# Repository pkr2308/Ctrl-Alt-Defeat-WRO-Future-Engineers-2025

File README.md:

# This repository has been moved to [CmdOptDefeat/fe25](https://github.com/CmdOptDefeat/fe25)

<picture>
  <source media="(prefers-color-scheme: dark)" srcset="https://github.com/pkr2308/Ctrl-Alt-Defeat-WRO-Future-Engineers-2025/blob/main/repo-assets/logo/ctrlaltdefeat-no-glow-no-bg-4096.png">
  <source media="(prefers-color-scheme: light)" srcset="https://github.com/pkr2308/Ctrl-Alt-Defeat-WRO-Future-Engineers-2025/blob/main/repo-assets/logo/ctrlaltdefeat-no-glow-no-bg-dark-4096.png">
  
</picture>

<br><br>Welcome to the repository for our entry in the WRO Future Engineers 2025 competition!
We are a team of 2 aspiring engineers building an autonomous robotic car using Raspberry Pi 5 & RP2040, equipped with various sensors and custom designs.

# About the Team
Adbhut Patil: TODO: expand 10th standard, interested in electronics, programming, aviation

Pranav Kiran Rajarathna: Pranav is currently sudying in the 11th grade(PCMC combination) and has been interested in Robotics for several years . He has participated in WRO in other categories in the past years. He was also part of Coding club in his school and built a few robotics projects for school events. His other interests include maths, physics, numismatics and history.

| __Team Photo__ |
|:-----------:|
||
| __Picture: Pranav (Left) and Adbhut (Right)__ |

# Project Overview
This project is our official entry for the Future Engineers category at the World Robot Olympiad 2025. Our goal is to construct a self-driving vehicle capable of navigating the track in both the Open and Obstacle Rounds. The programs are written in C++ and Python in the VSCode IDE, with the PlatformIO extension. OpenCV is used with the Raspberry Pi for object detection and navigation. This repository contains the programs, hardware description, schematics and design files of our solution.

# Hardware Components
- __Compute:__ Raspberry Pi 5 (main computer), Raspberry Pi 2040 (Waveshare RP2040-Zero, real-time control)
- __Sensors:__ 1D and 2D LiDAR, IMU, rotary encoders, Picamera
- __Actuators:__ N20 geared DC motor with encoder, MG996R 180° servo
- __Chassis:__ Commercially available base with 3D-printable additions (3D-design files included)
- __Electronics:__ Custom peripherals interface PCB for reliable connections to sensors

Note: The whole readme file is massive.
See [this section](https://github.com/pkr2308/Ctrl-Alt-Defeat-WRO-Future-Engineers-2025?tab=readme-ov-file#peripherals-interface-board) for more details about sensors on the peripherals interface board, and <link> for details about the RPi 5 and its sensors.

# Repository Structure
- [design-files](https://github.com/pkr2308/Ctrl-Alt-Defeat-WRO-Future-Engineers-2025/tree/main/design-files) : Contains the Bill of Materials, 3D-printable design files and hardware. Pictures and description of the robot and components are included.
- [initial-tests](https://github.com/pkr2308/Ctrl-Alt-Defeat-WRO-Future-Engineers-2025/tree/main/initial-tests) : Intial tests on various sensors to ensure accurate data collection and basic object detection algorithm.
- [hw](https://github.com/pkr2308/Ctrl-Alt-Defeat-WRO-Future-Engineers-2025/tree/main/hw) : Contains schematic and PCB files for the peripherals interface board.
- [sw](https://github.com/pkr2308/Ctrl-Alt-Defeat-WRO-Future-Engineers-2025/tree/main/sw) : Contains PlatformIO project for the peripherals interface board.
- [open-round](https://github.com/pkr2308/Ctrl-Alt-Defeat-WRO-Future-Engineers-2025/tree/main/open-round) : It contains the program files for the open round over various iterations and hardware setups. The final open round program is found in `sw/peripherals-board/src/divers`
- [repo-assets]() :
- [obstacle-round](https://github.com/pkr2308/Ctrl-Alt-Defeat-WRO-Future-Engineers-2025/tree/main/obstacle-round) : 
- [test-data-recordings/open-round](https://github.com/pkr2308/Ctrl-Alt-Defeat-WRO-Future-Engineers-2025/tree/main/test-data-recordings/open-round) : It contains data logs from various open round tests

> [!NOTE]
> Random files called `.lgd-nfy0` may be seen sometimes in varioues places. These were probably created by a typo a long time ago, and despite repeated deletion, they keep spawning everywhere in the Pi's cone of the repo! Just ignore them, if they occur. 

# System Architecture 

-	Raspberry Pi 5: It uses ROS2 and handles more complex tasks like object and colour detection, route planning, and the 2D LiDAR
-	RP2040 (Pi Pico): Handles real-time tasks (motor PID, encoder feedback, servo control, IMU, 1D LiDAR)
-	LiDARs: Used for detecting turn direction, obstacles and in parking
-	IMU: Gives yaw (and other orientations) of the robot in [0,360)
-	Motor/Servos: PWM and PI controls respectively for movement using sensor data, coordinated by the RP2040

## Mobility

- A commercially available metal [chassis base](https://www.elecrow.com/4wd-smart-car-robot-chassis-for-arduino-servo-steering.html) has been used with custom designed and printed parts. This chassis was selected mainly for its good steering system, mobility and customisabilty (there are lots of through holes through the base-frame). While the steering was retained, the remaining parts were custom designed.
- A link based steering system is used in the robot with a link-rod between the front wheel joints and another between a wheel joint and the servo. This steering system has been taken from the chassis without much modification due to its precision. A MG996R 180° servo has been used for the steering due to its high torque and accuracy, which improve mobility. 
- A single axle rear drive train is used for driving is used. A 200RPM N20 motor is used due to its speed and decent torque. A 1:1 gear ratio is used with a pair of brass gears. Bearings are used on the rear axle for smooth movement. A custom [rear drive holder](https://github.com/pkr2308/Ctrl-Alt-Defeat-WRO-Future-Engineers-2025/blob/main/design-files/N20%20Motor%20Holder.stl) is used to house all these parts.
- Both the servo and N20 motors are connected to the peripherals board. The servo is controlled using the standard library, while PWM is used for speed control of the motor.
- Turning Radius: Optimized for narrow WRO track corners, and is 32-33 cm.
- Build Choice Reasoning: Offers realistic car-like dynamics, ideal for FE challenge simulation.
[Design files](https://github.com/pkr2308/Ctrl-Alt-Defeat-WRO-Future-Engineers-2025/tree/main/design-files) contains all the other custom 3D-Design files (created on [TinkerCAD](https://www.tinkercad.com)) for mounting various compnents and systems onto the base chassis and one another.
[Robot assembly](https://github.com/pkr2308/Ctrl-Alt-Defeat-WRO-Future-Engineers-2025?tab=readme-ov-file#robot-assembly) instructions are below.
- Improvements: 
1. A uniform steering system. In the current model, the servo has to turn a greater angle left than right for the same angles of the wheels in each direction. This complicates driving algorithms to some extent. A better, but equally smooth steering system, maybe a rack-and-pinion, will solve these issues.
2. Better gear train. The current gears, though made of brass wear down quite easily for some unidentified reason. This causes slipping if there is more wear.
3. Reducing the turning radius. The current bot, while quite manoeuvrable has a large turn radius (almost 33-34cm). Reducing this would make taking tighter turns possible, improving error margins in the obstacle round. This can be done by bringing the drive train forward.

## Power

- A [Waveshare UPS Hat E](https://www.waveshare.com/wiki/UPS_HAT_(E)) is used for powering the robot. It uses 4 4000mAH 3.6V 21700 Li-ion batteries. (Different battery capacities may be used). All outputs are at 5V.
- The Pi is powered at a stable 5V via the POGO pins on the UPS Hat. The PiCamera and RPLidar are power from the Pi.
- The RP2040 and all connected sensors are powered through a USB A-C cable from the Pi to it.
- The total current draw for the obstacle round is around 600-630mA, and around 250-300mA for idle with the Pi.
- The peripherals board gets power directly from the UPS Hat through a USB-A cable that has been cut to get the power wires. This powers only the rear motor and steering servo.
- Improvements:
1. The UPS Hat that we are using has a weird anomaly. Although the batteries will have good voltage output and detected capacity, it will show the net remaining capacity to be very low. We have edited the code of the UPS library to not allow it run `sudo poweroff` when it misdetects such a situation.
2. Maybe not have the small switch on the board; closing it will cause these 2 systems to be connected, which could lead to some bad outcomes!

## Sensors

- __TFLuna LiDAR:__ These are 1D-LiDARs that are used to measure distances to the front, left, right (for driving) and back(parking) of the robot. They are connected to the RP2040. A separate section has been designed at the front of the robot to house all four LiDARs. Each LiDAR has 5 wires, grouped into 4+1 (I2C + GND) going into the peripherals board. These LiDARs were selected for their accuracy, small size and ease of use.
- __BNO055:__ This is the IMU we are using for orientation due to its reliability, accuracy and simplicity of use. It is connected to the RP2040, and is directly slotted into the peripherals board.
- __nRF24L01:__ This is the wireless module used for wireless communication during testing and debugging with the RP2040. Another custom module (telemetry board) is made for receiving the data. (Note : This is not plugged in for actual rounds). It is directly slotted into the peripherals board.
- __Motor encoders:__ The encoders give ticks each time they are trigerred by rotation of the motor shaft. Data from it is used for distance calculations. In our case, about 43 ticks corresponds to 1cm. The 4 encoder wires are grouped together and connected to the peripherals board.
- __Raspberry Pi Camera Module 3 Wide:__ It is used with the Pi for detecting the an obstacles. The camera is secured at four points for greater stability. With only two connection points, the camera could be easily turned due to the material properties of the Camera to Pi 5 connection wire. The higher mounting location allows it to detect obstacles from a large distance (almost 2m!) and plan accordingly. The Wide lens allows for a greater field of view. The NoIR version used to give odd red patches due to the lack of the IR filter in some test cases.
- __RPLidar A1:__ It is a 2D-LiDAR. It was supposed to be connected to the Pi and give distance all around the robot. However, we could not get it work Raspbian or any other OS. (It worked well with ROS though!) So, it is basically dead weight!
- Improvements: 
1. The RPLidar doesn't work well with the standard Raspbian OS on the Pi or with a computer, with values for many angles returned zero or being frozen. It seems to work fine on ROS though. Not sure what the issue is, but resoving this can improve ease of programming.
2. The 1D LiDARs are quite expensive. Ultrasonic sensors would have done for the sides.
3. The BNO055 does clock stretching, which causes issues on the I2C buses of most microcontrollers (thankfully not the RP2040). It also has a slight drifting tendency of a few degrees after a round. A IMU that does not have these issues and is easy to use will be more accurate and more flexible in use.

The [Bill of Materials](https://github.com/pkr2308/Ctrl-Alt-Defeat-WRO-Future-Engineers-2025/blob/main/design-files/Bill%20of%20Materials.md) contains all necessary parts/components and their sources.

## Obstacle Management

- This is done mainly using the camera feed from the PiCamera 3 Wide. The NoIR version tends to give red spot in places with lots of light due to lack of IR filter, which made it incompatible for this case.
- The OpenCV library (in Python3) is used for all the image manipulation and data extrapolation. HSV mode has been used for all the detecting, while images arer displayed in RGB. Sometimes, red may appear as blue due to use of BGR format used by camera to rercord. This is of no consequence, since it does not affect detection itself.
- Initially, the colour ranges for the obstacles, parking walls and side walls are identified. Interestingly, in our case, the 'magenta' parking walls show up as pure red.
- First, the region of interest (ROI) is taken as the bottom half of the feed (this is for our camera placement. May vary for other setups).
- Then, coloured masks (one each for red and green) are applied, followed by OpenCV's controur detection to detect surfaces. Data like position, height and width of the contours may be obtained from the other OpenCV methods.
- If the contours detected meet the required criteria (like size, height-width ratio), they are classified as obstacles. For our benefit, rectangles are drawn around the obstacles.
- Using the data available, including obstacle position, yaw and distance travelled, the required steering is calculated to pass the obstacle on the correct side, when not at a turn (Red - right, green - left)
- When the side chosen is preceded by a turn, the turn is initiated at a predefined distance from the wall ahead. (Ex: Clockwise round, green -> turn early)

Improvements:
1. The RPLidar might have been used effectively with better drivers with the standard Raspbian OS.
2. A more accurate formula to convert y-coordinate of obstacle obtained by the camera into actual distance

# Robot Assembly

It will be helpful to refer to the pictures of the completed model for the following steps. Most screws used are of 3M type (3mm dia.). At some places in our robot, internal hex screws are used in places where plus(+) screws of the right length were not available.
1. Add the front wheels and steering link to the robot
2. Attach the servo motor and connect it to the steering link
3. Print all design files
4. Attach the N20 motor onto the rear drive with brackets. Fit a gear onto the motor.
5. Cut the rear axle to the appropriate length (around 96mm) and attach the rear axle with wheels and gear onto the rear drive.
6. Mount the rear drive onto the chassis.
7. Attach 6 pillar screws of length 26mm in the back and 2 of length 22mm in the front (adjacent to the servo)
8. Attach the middle plate at the 6 rear points, but not at the front. The peripherals board may be screwed on using 4 pillar screws.
9. Attach the TFLuna LiDARs to the front LiDAR holder section, followed by the RPLiDAR (remember to connect the USB adapter) with 22/24 mm screw pillars. Screw in the front points.
10. Attach the LiDAR holder section to the front of the chassis.
11. Attach the additional support section for the LiDAR holder to the 2 front middle plate points and 2 rear RPLidar points.
12. Screw in the RPLidar's extra micro-USB pin extender to the support section
13. Attach the two PiCamera holder parts to the rear of the Lidar support section, and screw in the camera (2M screws and nuts are needed)
12. Attach the top-most Raspberry Pi and UPS platform to the rear with screw pillars.
13. Attach the rear lidar holder with the rear lidar attached to it
14. Attach the Raspberry Pi with the UPS Hat to the top.
15. Make all wired connections by referring to schematic files.

# Peripherals Interface Board

The peripherals interface board goes between the Raspberry Pi and vehicle hardware. The board talks to three 1d TFLuna LiDARs, a 9-axis BNO055 IMU, the motor encoder, the drive motor, and the steering servo. It talks to the Pi over USB.

## Hardware
The board is a two-layer, 1.6 mm thick PCB designed in [KiCad](https://kicad.org) and manufactured by [Robu](https://robu.in).
TODO: Expand

## Software
The interface board was programmed in C++, with the C++ SDK from Raspberry Pi for the RP2040 chip. Code was flashed using the PlatformIO extension for the VSCode editor.

The codebase is designed to be modular, with easily swappable drivers for hardware abstraction. Algorithms do not need to know about specific hardware protocols or constraints

`main.cpp` loads in drivers, which implement virtual interface classes. `main.cpp` then initialises everything, and in a loop, gets data from the `SensoorManager`, passes that data to our drive algorithm, and outputs it to the `TargetController`, which commands the motor and steering servo.
Drivers are in `/src/drivers`, Interfaces are in `/src/interfaces/`, and utilities are in `/src/utils/`.

### Code Development Standards
To ensure easily testable, upgradeable, and clean code, a few standards were adhered to when writing code for the interface board.

- `main.cpp` must be as clean as possible.
  - Logic and code flow must be easy to understand.
- All hardware-specific things should be done inside a driver.
- Drivers must take in a standard unit as their input.
  - Drivers must not take in [magic numbers](https://en.wikipedia.org/wiki/Magic_number_(programming)).

TODO: Finish writing this

### Drivers
> [!NOTE]
> Hardware revision 1 drivers are incomplete, as the peripherals baord codebase was partly written when the switch from the prototype interface and the PCB occured, and drivers from that point on were only for the PCB (hardware revision 2).
A list of implemented drivers:
- `hwrev2_imu` : Implements `ISensor`. Driver for the BNO055. Gets orientation data processed by the BNO055's internal microcontroller.
- `hwrev2_lidar` : Implements `ISensor`. Driver for the TFLuna LiDARs. Returns a [0, 259] of distance data. The three LiDARs are mapped to `0`, `90`, and `270`. (This is a remnant of the original plan of connecting the RPLidar to the peripherals board, instead of to the Pi.)
- `hwrev2_motor_driver` : Implements `IMotorDriver`. Driver for the TB6612FNG dual-channel H-bridge motor driver. The driver only supports driving a single channel on the T66612FNG.
- `hwrev2_rf24_communication` :  Implements `ICommunication`. Driver for the nRF24L01+ radio used during development. Transmits vehicle data and gets commands from another nRF24L01+, connected to a computer.
- `hwrev2_single_lidar_open_round` : Implements `IDriveAlgorithm`. A port of our open round test algorithm. The name is misleading, the algorithm uses all three TFLunas.
- `hwrev2_steering_driver` : Implements `ISteeringDriver`. Driver for the MG996 steering servo. Takes in a degree input and coverts it to a 0-180 command with a conversion constant.
- `hwrev2_target_control` : Implements `ITargetControl`. Takes in a `VehicleCommand`, and either passes it directly through to the `ISteeringDriver` and `IMotorDriver`, or passes the command through a PID controller first.
- `hwrev2_uart_logger` :  Implements `ILogger`, Takes in a sender, message type, and a message string
- `hwrev2_vehicle_speed` : Implements `ISensor`. Gets vehicle distance from the motor encoder. Calculates speed using time between pulses.

### Interfaces

Interfaces are virtual classes which define certain functions. Drivers implement these classes. Code calls functions defined in the interface virtual class.

- `IDriveAlgorithm` : Takes in a `VehicleData` object, and returns a `VehicleCommand` object.
- `ILogger` : Constructs a message and prints it out on a UART bus. Takes in a sender string, a log type (information, warning, error) and the message.
- `IMotorDriver` : Takes in a speed value and outputs to a motor driver.
- `ISensor` :  A generic sensor object. Returns a vector of `SensorData` objects.
- `ISteeringDriver` :  Takes in a wheel steering angle, outputs to a steering mechanism.
- `ITargetControl`: Takes in a `VehicleCommand`, outputs to a motor and steering driver.

### Managers

Managers are classes that handle certain aspects of the vehicle. Certain structs have their header files in the `/src/managers` folder, even though they are not classes.

- `VehicleConfig` :  A struct containing information about the vehicle. A `VehicleConfig` struct is passed to all drivers asnd managers.
- `SensorData` :  A struct containing fields for all data that can be collected by the vehicle, and an enum which tells the caller what fields are being used.
- `SensorManager` :  A class which takes in an arbitrary number of sensors, collects data from them, and processes them into a `VehicleData` struct.
- `SensorStatus` :  A (currently unused) enumeration which defines keys for states a sensor can be in. 
- `Vec3f` :  A struct of three double-precisionn floating point numbers, used to represent three-axis values.
- `VehicleCommand` :  A struct defining a target speed and yaw value for the vehicle. Returned by a drive algorithm, passed to a `ITargetController`.
- `VehicleData` :  A struct containing processed vehicle data. Returned by a `SensorManager`.

## Utilities

- `SchedulerTask` : A class which calls a function periodically.
- `Schedular` : A class which takes in an arbitrary number of `SchedulerTask`s, and updates them.

# Raspberry Pi System

The Raspberry Pi system handles most tasks for the obstacle round, including unparking, obstacle detection and navigation.

## Raspbian Setup

We are using Raspbian Bookworm.
Run the following commands in the terminal
- $`sudo chmod 0700 /run/user/1000`
- $`sudo apt install software-properties-common`
- $`sudo apt install python3-launchpadlib`
- $`sudo apt install code`
- $`sudo apt upgrade code`
- $`sudo apt install idle3`
- $`sudo apt install python3-opencv`
- $`sudo apt install -y python3-libcamera python3-pyqt5 python3-picamera2`
- Refer [here](https://www.waveshare.com/wiki/UPS_HAT_(E)) to install UPS library to show details about the batteries.
- If the Pi is accidentally shut down, and git is not working, run the following: 
1. $`find .git/objects/ -type f -empty | xargs rm` - Cleaning
2. $`git fetch -p` - Restore missing objects
3. $`git fsck --full` - Verify
- It is advised to have RPiConnect for easy connection to the Pi.
- This reposittory is cloned on the Pi and the obstacle round program is added to the startup sequence.

## Adding Programs to Startup

The method used here involves running executables on startup. Refer [`initial-tests/startup-test/`](https://github.com/pkr2308/Ctrl-Alt-Defeat-WRO-Future-Engineers-2025/tree/main/initial-tests/startup-test) for the code.
1. Create the python file
2. Create a launcher script, like the one in the initial test file, that ends in `.sh`. Ensure the launcher is working with `./(launcher-name).sh` in its directory.
3. In the launcher script, navigate to the directory of the python file and run it with `sudo python3 (file-name).py`. Then return to user directory
4. In the directory with launcher script, make it executable by running `sudo chmod 755 (launcher-name).sh`
5. Run `sudo crontab -e` (you can use nano to edit it), and add `@reboot sh /home/(user)/(path to launcher)/(launcher-name).sh` at the end.
6. Restart the Pi (`sudo reboot`) to check if it works.

## PiCamera 3

The Raspberry Pi Camera Module 3 Wide is used for obstacle detection. It is placed high up to have a good view. (We actually only use the bottom half of the frame!)

## Serial Communication

The Pi communicates with the RP2040 over the serial. When the Pi sends a command (speed and steering), the RP2040 sends back data (like yaw, lidar distance, turn direction etc.)

# Open Round

Refer to `sw/peripherals-board/src/drivers/hwrev2/hwrev2_single_lidar_open_round.cpp and .hpp` files for program.

## Header File

Public includes the logger (for debugging), vehicle command (for driving) and sets direct control of servo (A target yaw value is generally given). Private includes setup of variables for driving, turning, servo, IMU, 1D LiDARs and IMU-based straight follower. 

## Implementation File

### Initialisation
- Sets up logging
- Sets initial speed and steering

### Turn Detection & Execution:
- Uses front LiDAR to detect when to start a turn (if obstacle is close).
- Decides turn direction (left/right) based on side LiDARs (First turn only)
- Turns are started considering factors of distance available, yaw, current section and distance travelled. 
- Adjusts steering (servo position) during turn based on yaw and for greater smoothness.
- After each turn, resets variables and prepares for the next segment. Target yaw and threshold distance may be altered for better accuracy and counter drifting.
- The idea to stick to the outer wall, so even with randomisation, the extended inner wall is not hit

### Straight Movement:
- When not turning, uses gyro (yaw) to follow a straight path.
- Applies proportional-integral correction to steering for accurate straight-line travel.

### Turn Direction Logic:
- Chooses clockwise or anticlockwise based on which side has more open space (LiDAR difference).
- Sets different thresholds for smoother turns depending on direction.

### Stopping 
- Counts turns; after 12 turns (3 rounds), slows down and stops at the start section.

## Flow
1. Start moving straight.
2. Decide turn direction using side LiDARs. (For first turn only)
3. Detect distance to wall ahead with front LiDAR.
4. Execute turn when condition are met, adjust steering and target yaw.
5. After turn, resume straight movement with PI control.
6. Repeat for 3 rounds (12 turns).
7. After final round, slow down and stop in the start section.

# Acknowledgements

We would like to thank
- YoLabs Team:
- Raspberry Pi Foundation:
- OpenCV :

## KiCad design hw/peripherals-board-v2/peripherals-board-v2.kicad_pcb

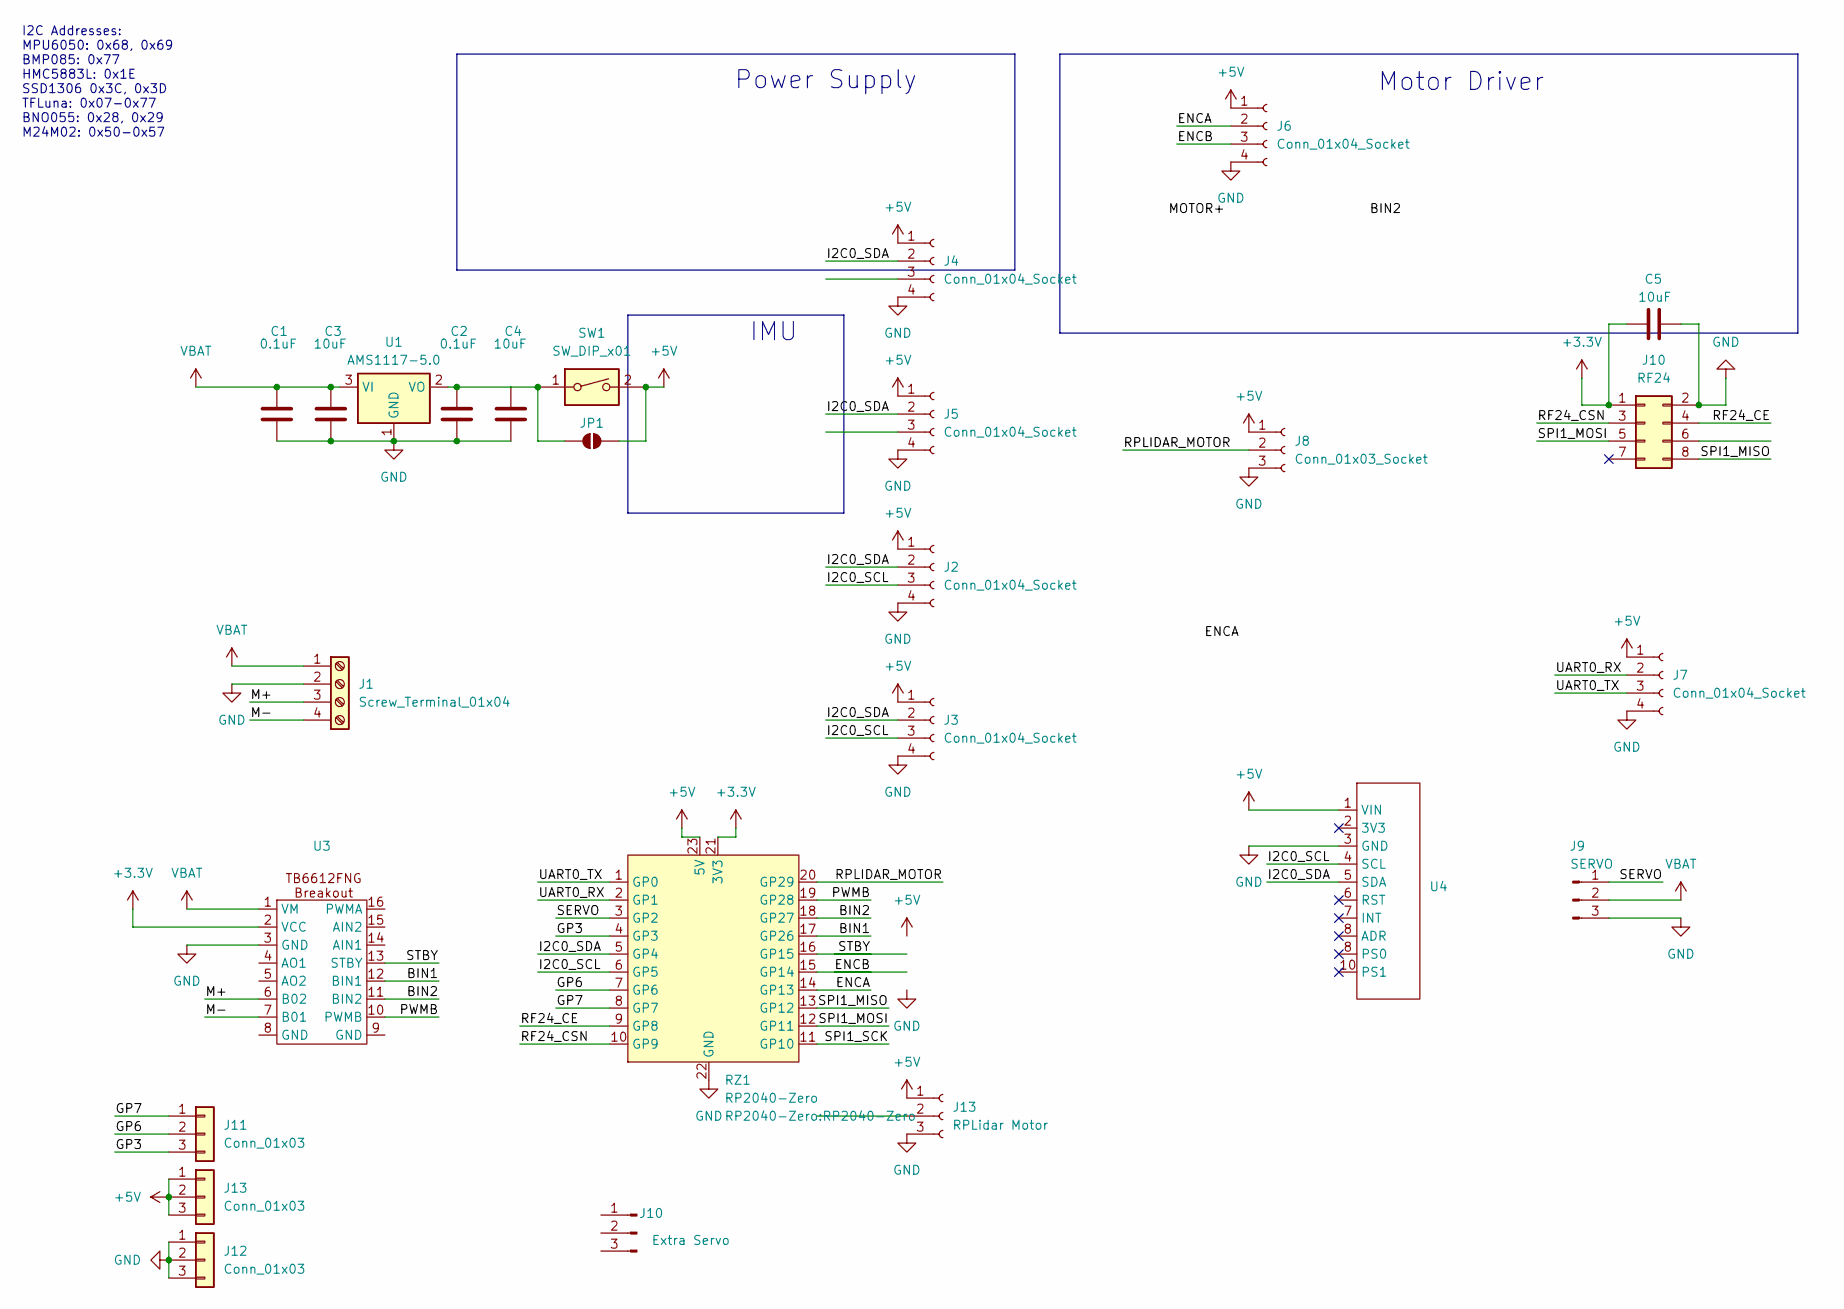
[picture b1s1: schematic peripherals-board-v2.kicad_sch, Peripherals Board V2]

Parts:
C1, C2: 0.1uF; C_0805_2012Metric_Pad1.18x1.45mm_HandSolder
C3, C4, C5: 10uF; C_0805_2012Metric_Pad1.18x1.45mm_HandSolder
J1: Screw_Terminal_01x04; ScrewTerminal_01x04_P5mm
J2, J3, J4, J6, J7: Conn_01x04_Socket; JST_XH_01x04_Horizontal_NoFlange
J5: Conn_01x04_Socket
J8: Conn_01x03_Socket; JST_XH_01x03_Horizontal_NoFlange
J9: SERVO; PinHeader_1x03_P2.54mm_Vertical
J10: RF24; PinSocket_2x04_P2.54mm_Vertical
J11, J12, J13: Conn_01x03; PinSocket_1x03_P2.54mm_Vertical
JP1: SolderJumper_2_Open; SolderJumper-2_P1.3mm_Open_TrianglePad1.0x1.5mm
RZ1: RP2040-Zero
SW1: SW_DIP_x01; SW_DIP_SPSTx01_Slide_6.7x4.1mm_W7.62mm_P2.54mm_LowProfile
U1: AMS1117-5.0; SOT-223-3_TabPin2
U3: TB6612FNG-breakout
U4: BNO055-breakout

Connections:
+3.3V: C5.1, J10.1, RZ1.21 (3V3), U3.2 (VCC)
/BIN1: RZ1.17 (GP26), U3.12 (BIN1)
/BIN2: RZ1.18 (GP27), U3.11 (BIN2)
/ENCA: J6.2, RZ1.14 (GP13)
/ENCB: J6.3, RZ1.15 (GP14)
/GP3: J11.3, RZ1.4 (GP3)
/GP6: J11.2, RZ1.7 (GP6)
/GP7: J11.1, RZ1.8 (GP7)
/I2C0_SCL: J2.3, J3.3, J4.3, J5.3, RZ1.6 (GP5), U4.4 (SCL)
/I2C0_SDA: J2.2, J3.2, J4.2, J5.2, RZ1.5 (GP4), U4.5 (SDA)
/M+: J1.3, U3.6 (B02)
/M-: J1.4, U3.7 (B01)
/PWMB: RZ1.19 (GP28), U3.10 (PWMB)
/RF24_CE: J10.4, RZ1.9 (GP8)
/RF24_CSN: J10.3, RZ1.10 (GP9)
/RPLIDAR_MOTOR: J8.2, RZ1.20 (GP29)
/SERVO: J9.1, RZ1.3 (GP2)
/SPI1_MISO: J10.8, RZ1.13 (GP12)
/SPI1_MOSI: J10.5, RZ1.12 (GP11)
/SPI1_SCK: J10.6, RZ1.11 (GP10)
/STBY: RZ1.16 (GP15), U3.13 (STBY)
/UART0_RX: J7.2, RZ1.2 (GP1)
/UART0_TX: J7.3, RZ1.1 (GP0)
unnamed: C2.1, C4.1, JP1.1 (A), SW1.1, U1.2 (VO)
VBAT: C1.1, C3.1, J1.1, J9.2, U1.3 (VI), U3.1 (VM)

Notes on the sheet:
Power Supply
Motor Driver
IMU
I2C Addresses: MPU6050: 0x68, 0x69 BMP085: 0x77 HMC5883L: 0x1E SSD1306 0x3C, 0x3D TFLuna: 0x07-0x77 BNO055: 0x28, 0x29 M24M02: 0x50-0x57

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
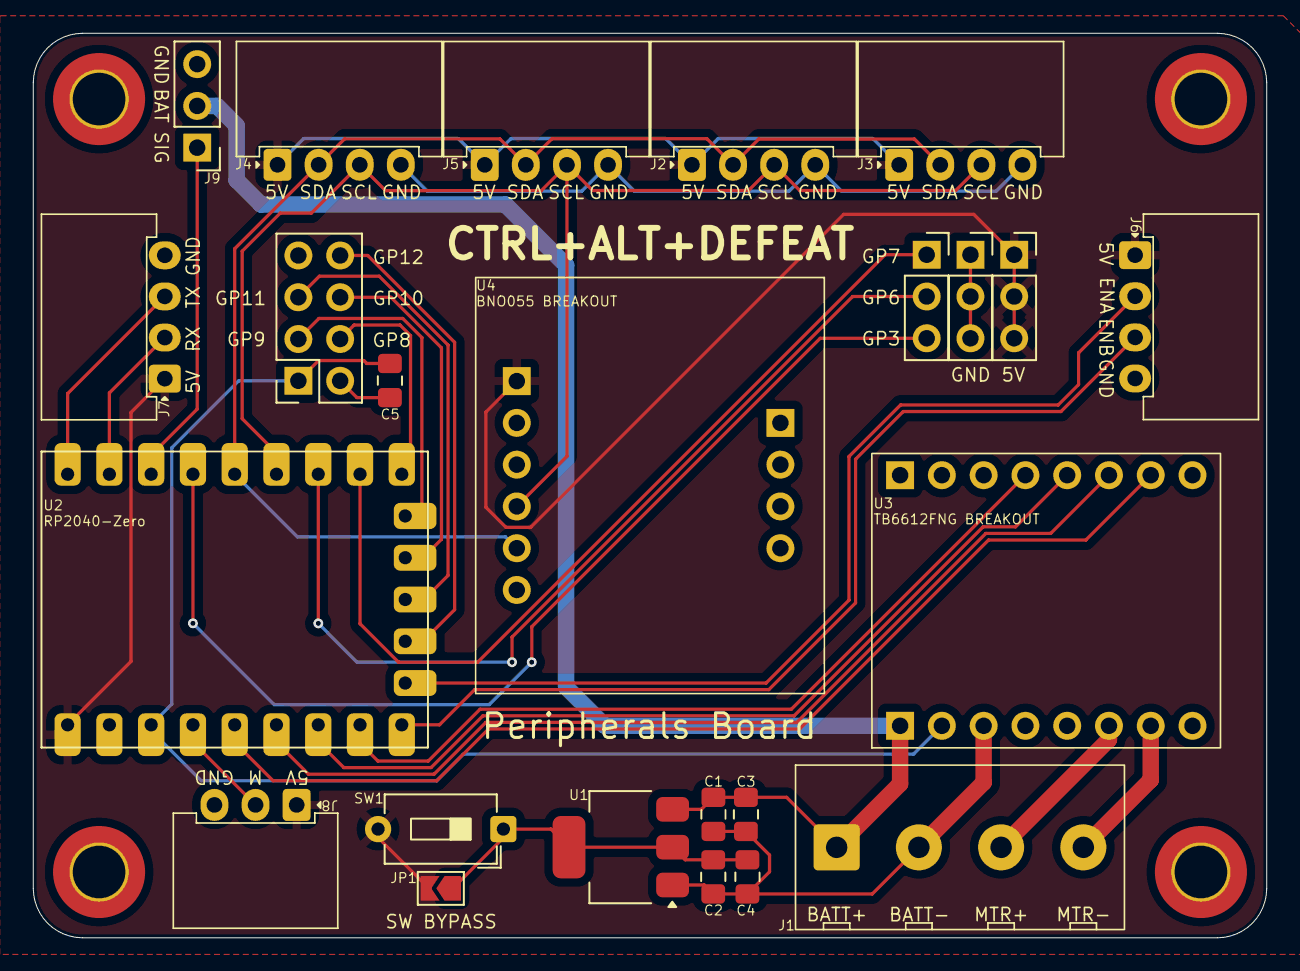
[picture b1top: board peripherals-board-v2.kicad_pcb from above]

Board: 2 copper layers, 75.0 x 55.0 mm, 24 parts (0 on the bottom side), 27 nets.

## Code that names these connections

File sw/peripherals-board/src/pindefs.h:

/*

  pindefs
  Pin definitions for peripherals board
  See /hw/peripherals-board for schematic

  Written by DIY Labs

*/

#pragma once

#define PIN_RGB_BUILTIN       16

#define PIN_TB6612_PWMB       26
#define PIN_TB6612_BIN1       28
#define PIN_TB6612_BIN2       27
#define PIN_TB6612_STBY       29

#define PIN_STEERING_SERVO    12

#define PIN_MOTOR_ENCA        2
#define PIN_MOTOR_ENCB        3

#define PIN_RX_CH1            15
#define PIN_RX_CH2            14

#define PIN_I2C0_SCL          1
#define PIN_I2C0_SDA          0
#define PIN_I2C1_SCL          11
#define PIN_I2C1_SDA           10

#define PIN_LIDAR_SERVO       4

#define PIN_SPI0_SCK 6
#define PIN_SPI0_MOSI 7
#define PIN_SPI0_MISO 4
#define PIN_RF24_CE 5
#define PIN_RF24_CSN 8

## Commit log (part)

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2025-06-29 Add files via upload
    These are the initial test files for colour detection using OpenCV
2025-06-29 Create new folder for initial tests of hardware/program
2025-06-29 Create folder for camera tests
2025-06-29 Add files via upload
    OpenCV colour and edge detection files
2025-06-29 Create folder for RPi camera tests
2025-06-29 Add files via upload
    Initial picamera tests with Raspberry Pi
2025-07-01 Create PlatformIO project for peripherals board
2025-07-01 Create KiCad project for peripherals board
2025-07-01 Add components to KiCad schematic, update .gitignore
2025-07-02 Change to RP2040-Zero symbol, create Processing sketch for telemetry viewer
2025-07-03 Create folder for design files of the model
2025-07-03 Add design file for motor holder
2025-07-03 Created list of components used for testing and making the model
2025-07-04 Add files via upload
    Adding test files for BNO055 gyroscope, accelerometer and magnetometer
2025-07-05 Update schematic to match board
2025-07-05 Create files for SensorManager and CommManager
2025-07-05 Create files for drivers
2025-07-05 Add files via upload
    Adding files for testing of all sensors and motors with Arduino with Motor controller shield, servo, lidar and IMU
2025-07-05 Implement sensor manager
2025-07-06 Implement MPU6050 driver
2025-07-06 Test data from MPU6050 and BMP085 drivers, remove HMC driver files
2025-07-06 Implement LiDAR driver
2025-07-06 Create temporary function to drive from FlySky RX
2025-07-06 Create struct for vehicle state
2025-07-06 First program for open round
    First program for open round using Arduino, TFLuna Lidar, IMU and chassis
2025-07-07 Commit Sunday changes
2025-07-07 Add library for RP2040-zero
2025-07-09 Create symbol and footprint for TB6612 breakout board
2025-07-09 Link T6612 breakout footprint to symbol
2025-07-09 Create symbol and footprint for GY-87
2025-07-09 Create folder for TF Luna tests
2025-07-09 Program to change I2C address of TF Luna
2025-07-09 Rename TFLuna_Test.xlsx.ino to TFLuna_Test.ino
2025-07-10 Add PCB lock file to gitignore
2025-07-10 Change URL to lowercase
2025-07-10 Create fill both layers for 5v and GND
2025-07-11 Routing changes to connect vreg to 5v plane
2025-07-11 Create folder for open round challenges
2025-07-11 Intial commit
2025-07-11 Fixing stopping and steering issues
2025-07-11 Reroute PCB
2025-07-11 Updating calibration
2025-07-12 Initial commit for dat via wifi
2025-07-13 Swap left LiDAR and radio input connectors
2025-07-13 Create PlatformIO project for open round PID test
2025-07-13 Add libraries to platformio.ini
2025-07-13 Include libraries
2025-07-13 PID Controller with servo output, drive motor with constant speed
2025-07-13 Tuned PID controller
2025-07-14 Create footprint and symbol for BNO055 breakout, prototype new layout
2025-07-14 Add connector for RPLidar in schematic
2025-07-15 Update peripherals board schematic and layout
2025-07-15 Export gerber files, update interactive BOM
2025-07-15 Change silkscreen, regenerate gerber and ibom
2025-07-15 Zip up gerber files
2025-07-15 Basic webpage with data
2025-07-16 Generate drill files flor PCB
2025-07-16 Create PlatformIO project for peripherals board V2
2025-07-18 Create PlatformIO project for telemetry adapter
2025-07-19 Add fields to datastruct
2025-07-19 Get BNO055 data and send over RF
2025-07-19 Print data over serial
2025-07-19 Testing anticlockwise
2025-07-19 Updated open round
2025-07-20 Print BNO calibration data
2025-07-20 Test commit
2025-07-20 Move radio init logic into funtion
2025-07-20 Move radio comm into function
2025-07-20 Add heartbeat bool to data
2025-07-20 Toggle heartbeat
2025-07-20 Toggle heartbeat every 100 ms
2025-07-20 Get commands from serial
2025-07-20 Change heartbeat to millis
2025-07-20 Add delay to improve issues
2025-07-22 Initial commit for multiple lidars
2025-07-23 Create SerialStudio project
2025-07-23 Clean peripherals board project
2025-07-23 Add Doxygen file description to main.cpp
2025-07-25 Create configuration structs
2025-07-25 Add include path of configuration library to build flags
2025-07-25 Define class for powertrain manager
2025-07-25 Sync commit
2025-07-27 Implement motor driver interface and driver
2025-07-27 Implement steering driver interface and driver
2025-07-27 Implement SensorManager
2025-07-27 Define VehicleCommand struct and interface for drive algorithms
2025-07-27 Move hwrev1-specific includes into hwrev1 include file
2025-07-27 Remane SensorStatus to Status
2025-07-27 Initial commit to stay in the middle of path
2025-07-29 Move Open_Round_V1.ino
2025-07-29 Update Single_Lidar_Wifi.ino challenges
2025-07-29 Update rear drive section design
2025-07-29 Add hw/sw folder description to README
2025-07-29 Create Scheduler class for handling timed reoccuring functions
2025-07-30 Create interface for target control
2025-07-30 Implement basic target control driver
2025-07-31 Add limits section to config
2025-08-03 Initial tests for RPLidar A1 using Adafruit library. A venv with the library and system-site-packages has been created
2025-08-03 Better measurements, and using Pi 5 instead of 4B
2025-08-03 Multiple LiDARs won't work with Arduino
2025-08-03 Add distance calculatio
2025-08-03 Try adding extensions.json to gitignore through VSCode
2025-08-03 Implement PID controller for steering
2025-08-03 Create files for single LiDAR open round driver
2025-08-03 Remove comments from drive algorithm
2025-08-03 Init drive algorithm in setup
2025-08-03 Update telemetry block description
2025-08-03 Add feature to ITargetControl to allow for direct control
2025-08-03 Add encoder position to vehicle data, print vehicle data
2025-08-03 Single lidar test
2025-08-03 Implement debugPrintVehicleData
2025-08-05 Change uint16_t to int16_t to avoid underflowing, add temp code to drive from external radio
2025-08-05 Remove debug print in hw_rev_2_MotorDriver::driveMotor
2025-08-05 Update design files
2025-08-05 Add start button
2025-08-05 Add documentation comments
2025-08-05 Add full path to doxyfile STRIP_FROM_PATH
2025-08-06 RP2040 does not show up as a USB device
2025-08-06 Experimental RF24 telemetry driver
2025-08-06 Update for multiple Lidars
2025-08-06 Implement speed calculation from motor encoder
2025-08-08 Get commands from drive and radio
2025-08-08 Sync
2025-08-08 Pass debug logger to drive algorithm
2025-08-08 Updated frront 1D and 2D Lidars' holder
2025-08-09 Pass debug logger to drivers
2025-08-10 Create functions for printing data and commands over UART debug
2025-08-10 Open round trial with fixed direction
2025-08-10 Reduce speed
2025-08-10 Inhibit speed, reverse encoder position
2025-08-10 More debugging
2025-08-10 Front lidar dist
2025-08-10 Target yaw is set.
2025-08-10 Change target control driver to command {-90, 90} to servo driver
2025-08-10 Check conditions for stopping turn
2025-08-10 Change speed and steering protocol calls
2025-08-10 Fix encoder value data reading
2025-08-10 Target yaw was limited to 256 by 8 bits, changed to 16
2025-08-10 un-negate encoder
2025-08-10 Set turnDir back to 0
2025-08-10 Turn dir identification
2025-08-10 Remove else
2025-08-11 Set lidar data to 16bits from 8
2025-08-11 Turn direction was set to the opposite of true value
2025-08-12 Send imu calib over radio telem, wait for BOOTSEL button press before driving
2025-08-12 Update single lidar
2025-08-12 Initial commit for multiple lidars for open round
2025-08-12 For multiple lidars, some config
2025-08-12 Yaw from 0 - 360, can't fit in 8 bit
2025-08-12 Transmit telemetry and drive
2025-08-12 Send buggy vehicle speed over radio
2025-08-12 Turning updates
2025-08-12 Add file extension to data file
2025-08-12 Commit more test recordings
2025-08-12 Commit run data
2025-08-12 Transmit calculated distance
2025-08-12 More conditions for turning, smoother turns
2025-08-12 Make in-run changes to target yaw and distance values
2025-08-12 Anticlockwise also added
2025-08-12 Copy open round code from sw to Open Round folder
2025-08-12 Rename folder
2025-08-12 Include more comments for documentation
2025-08-12 Documentation for open round
2025-08-12 Realised 9 square sections are there, not 8 trapeziums
2025-08-13 Upload test image of peripherals board PCB design
2025-08-13 Trim corners of peripherals board design screenshot
2025-08-13 Upload image
2025-08-13 Update README, forgot to upload design file earlier
2025-08-14 Crop RPi images
2025-08-14 Add raw photos of vehiclr from camera
2025-08-14 Crop all photos
2025-08-14 Update image test markdown file
2025-08-14 Fix heading error in image test file
2025-08-15 Drive from serial commands
2025-08-15 Constrain serial command
2025-08-15 Bidirectional comms with nRF24, drive from telemetry adapter board's serial
2025-08-16 Remove unnecessary zeroes from data
2025-08-16 Change out PCB design image to real life image of peripherals board in README
2025-08-17 Replace erroneous elf files with uf2 files for nRF binaries
2025-08-17 Add team photo to README
2025-08-17 Add cimpiled binaries for Serial drive and open round, add team photo
2025-08-17 Create temporary symbols and layout for vehicle wiring schematic
2025-08-17 Add docs for interfaces, managers, and utilities in README
2025-08-17 Update URL of images
2025-08-17 Add link to Wikipedia article about magic numbers
2025-08-17 Update README on RPi Sys and ROS
2025-08-17 Add names to photo
2025-08-17 Update formatting for photo
2025-08-17 Update opencv tests to work with PiCamera 3 (NoIR)
2025-08-18 Needed Libs in Pi
2025-08-18 Find colour of blocks in hsv
2025-08-18 Finding HSV values easier
2025-08-18 Find the HSV ranges for blocks as per PiCam 3
2025-08-18 Serial communication of Pi's side
2025-08-19 Create variables for Micro ROS
2025-08-19 Commit broken driver
2025-08-19 Update black colour ranges to detect walls
2025-08-19 Update camera preview size
2025-08-19 Flesh out Serial driver, send one line of data when new command is received
2025-08-19 Invert encoder
2025-08-19 Serial communication of Pi with RP2040
2025-08-19 Update obstacle detection
2025-08-19 RPLidar Tests
2025-08-20 Update Bill of Materials
2025-08-20 New design files for holding the PiCamera and UPS Hat
2025-08-20 Update README file
2025-08-21 Update contour detection with colours
2025-08-21 Applying edge and contour detection of recognised colour areas
2025-08-21 Add Doxygen note to Micro ROS driver
2025-08-21 Commit open round PID test files (?)
2025-08-21 Check for coloured contours only in ROI
2025-08-21 Detect the nearest obstacle colour and position
2025-08-21 Add logo prototype SVG
2025-08-21 Probe configured I2C adresses on boot, print results over debug port
2025-08-21 Trying to navigate around obstacles
2025-08-21 Update README and other changes
2025-08-22 Test commit on new branch
2025-08-22 Update navigation algorithm, Clean up code
2025-08-22 Rename folders for structure
2025-08-22 Update basic nav to include gyro straight, multiple obstacles
2025-08-22 Add logo to README
2025-08-22 Embed logo in README
2025-08-22 Add no-glow logo to README for comparison
2025-08-22 Update battery info in readme
2025-08-22 Export logo versions with black text
2025-08-22 Add theme-based conditional for logo in README
2025-08-22 Add LiDAR to the back too for parking
2025-08-22 Directions to pass obstacles were wrong
2025-08-23 Create driver and interface for color LED, create driver and parking module, transmit millis over radio
2025-08-23 Repeated crash/hangs on RP2040
2025-08-23 Make updates to oobstacle round programs
2025-08-23 Checklist before round (bot inspection)
2025-08-23 Add more debug messages to drivers, get data from all four LiDARs
2025-08-24 Add debug messages in LiDAR driver update function
2025-08-24 Modify checklist, loose connection on RP2040 carrier is not relevant with soldered PCB
2025-08-24 Add instruction field to VehicleCommand, fix text error in LiDAR debug log
2025-08-24 Add status_t return to ISensors
2025-08-24 Ping LiDARs on I2C on boot
2025-08-24 Create files for unpark algorithm
2025-08-24 Better obstacle detection
2025-08-24 Update checklist
2025-08-24 Create checklist for open round
2025-08-24 Update basic nav with single obstacle
2025-08-24 Update other readme/checklists structure
2025-08-24 Updates to make things clearer
